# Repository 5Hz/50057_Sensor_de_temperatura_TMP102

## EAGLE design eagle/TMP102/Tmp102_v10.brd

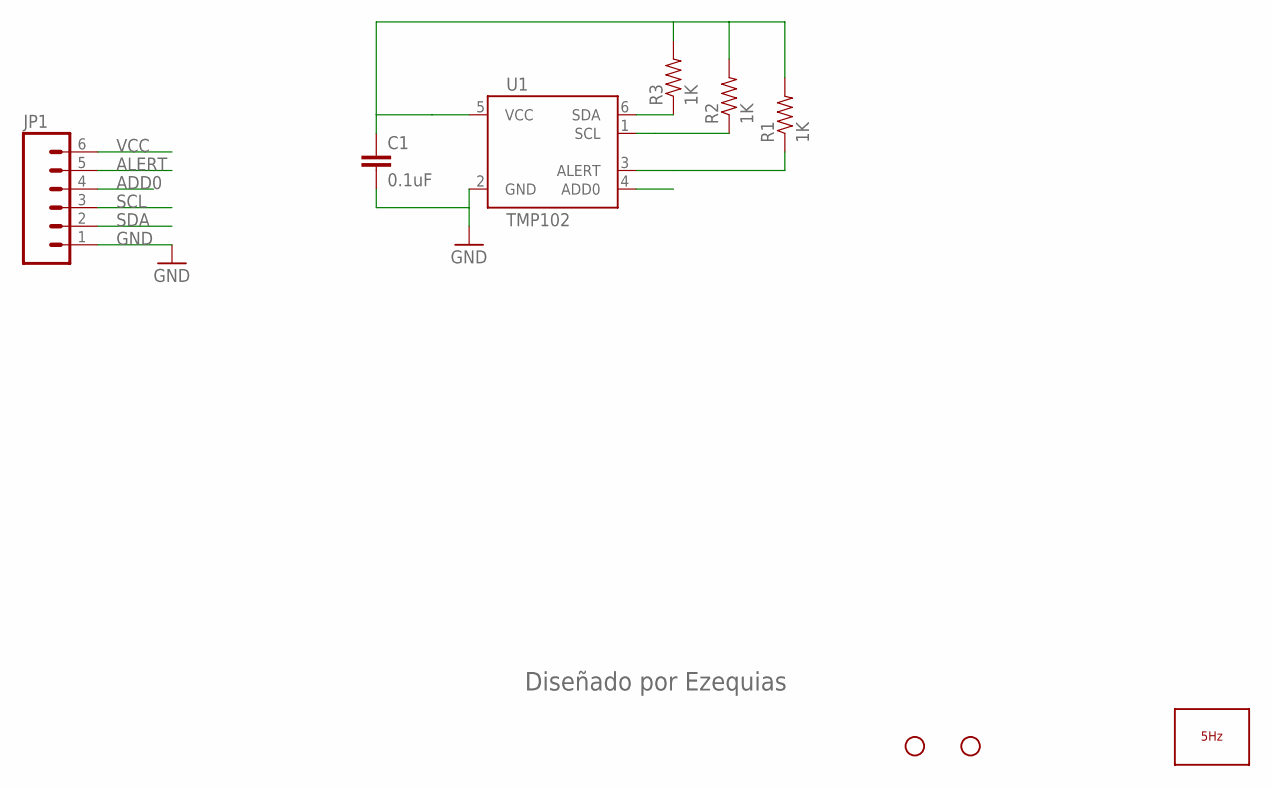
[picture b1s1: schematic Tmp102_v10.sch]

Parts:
C1: 0.1uF; 0603-CAP
JP1: M06SIP; 1X06
JP2, JP3: STAND-OFF
LOGO1: LOGO_5HZ_MAIN_5MM; 5HZ_LOGO_MAIN_5MM
R1, R2, R3: 1K; 0603-RES
U1: TMP102; SOT563

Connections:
ADD0: JP1.4, U1.4 (ADD0)
ALERT: JP1.5, R1.1, U1.3 (ALERT)
GND: C1.2, JP1.1, U1.2 (GND)
SCL: JP1.3, R2.1, U1.1 (SCL)
SDA: JP1.2, R3.1, U1.6 (SDA)
VCC: C1.1, JP1.6, R1.2, R2.2, R3.2, U1.5 (VCC)

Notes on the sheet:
Diseñado por Ezequias

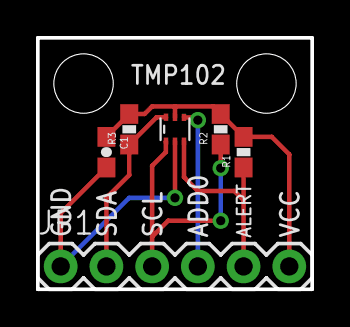
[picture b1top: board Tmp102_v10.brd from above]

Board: 2 copper layers, 15.2 x 14.0 mm, 9 parts (1 on the bottom side), 6 nets.

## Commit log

2014-01-13 creación

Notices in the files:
parts and their libraries:
SparkFun: Licensing: CC v3.0 Share-Alike You are welcome to use this library for commercial purposes.
